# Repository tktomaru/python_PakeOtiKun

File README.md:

# パケ落ちくんとは？

パケ落ちくんはネットワークエミュレーターです。
Lanの途中に挟むことで、ネットワークに対し以下のことができます。

- 遅延(DELAY)
- 廃棄(LOSS)
- 破壊(CORRUPT) : PakeOtiKun4とPakeOtiKunRSが対応
- 重複(DUPLICATION) : PakeOtiKun4とPakeOtiKunRSが対応
- 並び替え(REORDERING) : PakeOtiKunRSが対応

# ブログ

# パケ落ちくんソースコード

- PakeOtiKun.py : DSAS様の作成されたものと同じものをpythonにしました
- PakeOtiKun4.py : PakeOtiKunにおいて可変抵抗が2つだったものを4つにしたものです
- PakeOtiKunRS.py : 可変抵抗は4つでロータリースイッチを追加したものです

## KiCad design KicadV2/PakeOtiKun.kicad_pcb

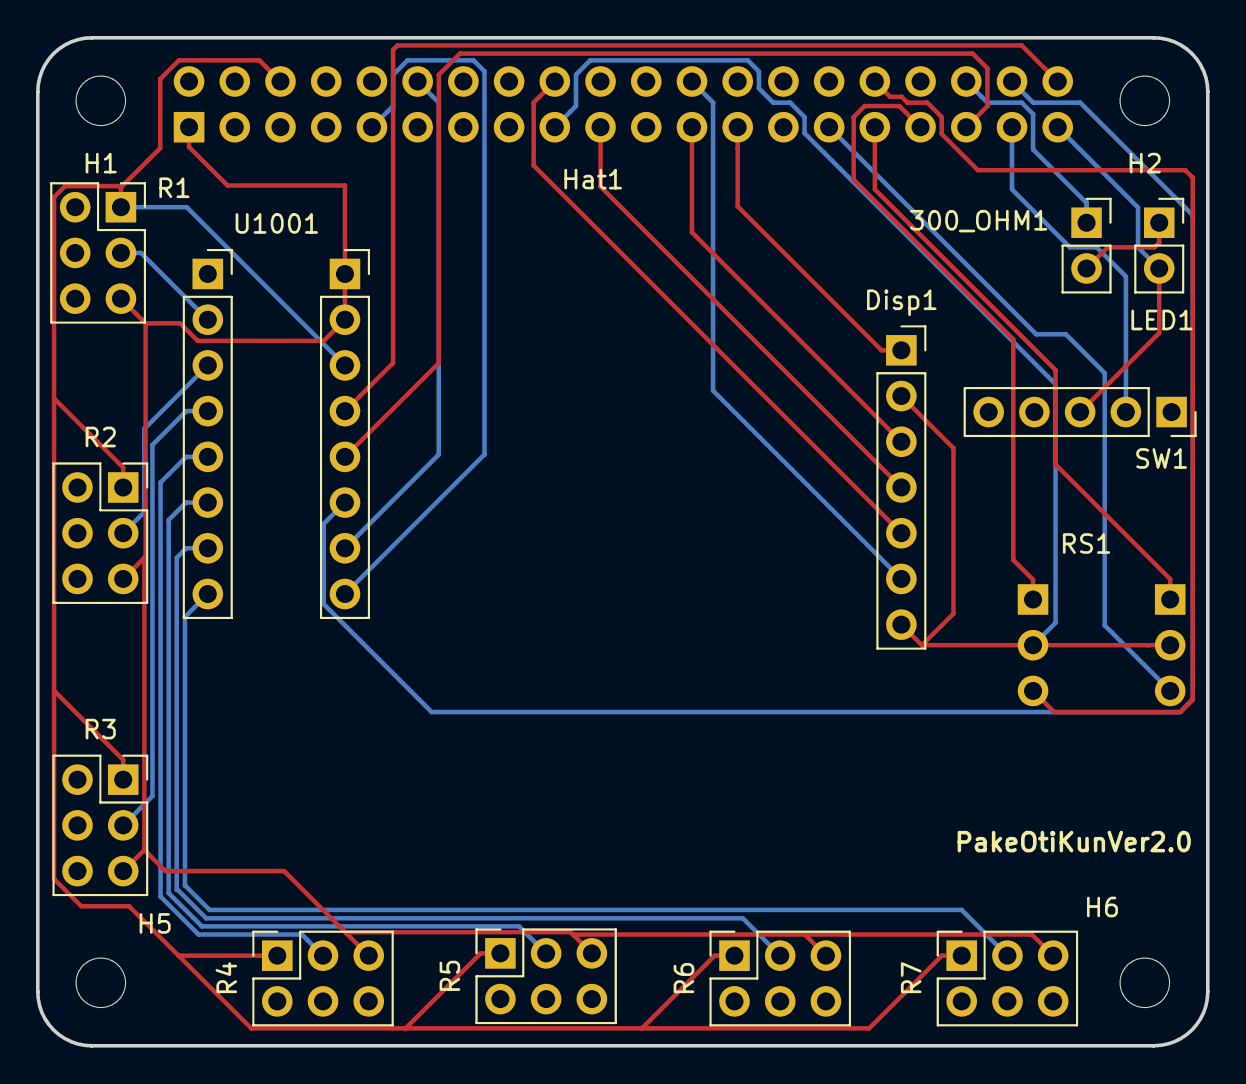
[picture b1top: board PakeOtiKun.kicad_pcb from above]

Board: 2 copper layers, 65.0 x 56.0 mm, 18 parts (1 on the bottom side), 28 nets.

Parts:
300_OHM1: Conn_01x02_Female; PinSocket_1x02_P2.54mm_Vertical
Disp1: Conn_01x07_Female; PinSocket_1x07_P2.54mm_Vertical
H1, H2, H5, H6: MountingHole; MountingHole_2.75mm_NoPad
Hat1: Raspberry_Pi_2_3; Raspi
LED1: LED; PinSocket_1x02_P2.54mm_Vertical
R1, R2, R3, R4, R5, R6, R7: Conn_02x03_Counter_Clockwise; PinSocket_2x03_P2.54mm_Vertical
RS1: 42J12ZB; RS
SW1: Conn_01x05_Female; PinSocket_1x05_P2.54mm_Vertical
U1001: MCP3208

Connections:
unnamed: 300_OHM1.1, Hat1.36
unnamed: 300_OHM1.2, LED1.1
unnamed: Disp1.1, Hat1.25
unnamed: Disp1.2, Disp1.7, Hat1.17, RS1.C
unnamed: Disp1.3, Hat1.23
unnamed: Disp1.4, Hat1.19
unnamed: Disp1.5, Hat1.18
unnamed: Disp1.6, Hat1.24
unnamed: Hat1.1, R1.5, R2.5, R3.5, R4.5, R5.5, R6.5, R7.5, U1001.15, U1001.16
unnamed: Hat1.6, R1.1, R2.1, R3.1, R4.1, R5.1, R6.1, R7.1, U1001.14
unnamed: Hat1.9, U1001.9
unnamed: Hat1.12, U1001.10
unnamed: Hat1.29, RS1.2
unnamed: Hat1.31, RS1.8
unnamed: Hat1.32, RS1.4
unnamed: Hat1.33, RS1.1
unnamed: Hat1.35, U1001.12
unnamed: Hat1.37, SW1.2
unnamed: Hat1.38, U1001.11
unnamed: Hat1.39, LED1.2, SW1.3
unnamed: Hat1.40, U1001.13
unnamed: R1.3, U1001.2
unnamed: R2.3, U1001.3
unnamed: R3.3, U1001.4
unnamed: R4.3, U1001.5
unnamed: R5.3, U1001.6
unnamed: R6.3, U1001.7
unnamed: R7.3, U1001.8

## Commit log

2022-12-18 開発／初期コミット
2022-12-18 開発／README.mdを修正
2023-08-05 動かないV2を削除
